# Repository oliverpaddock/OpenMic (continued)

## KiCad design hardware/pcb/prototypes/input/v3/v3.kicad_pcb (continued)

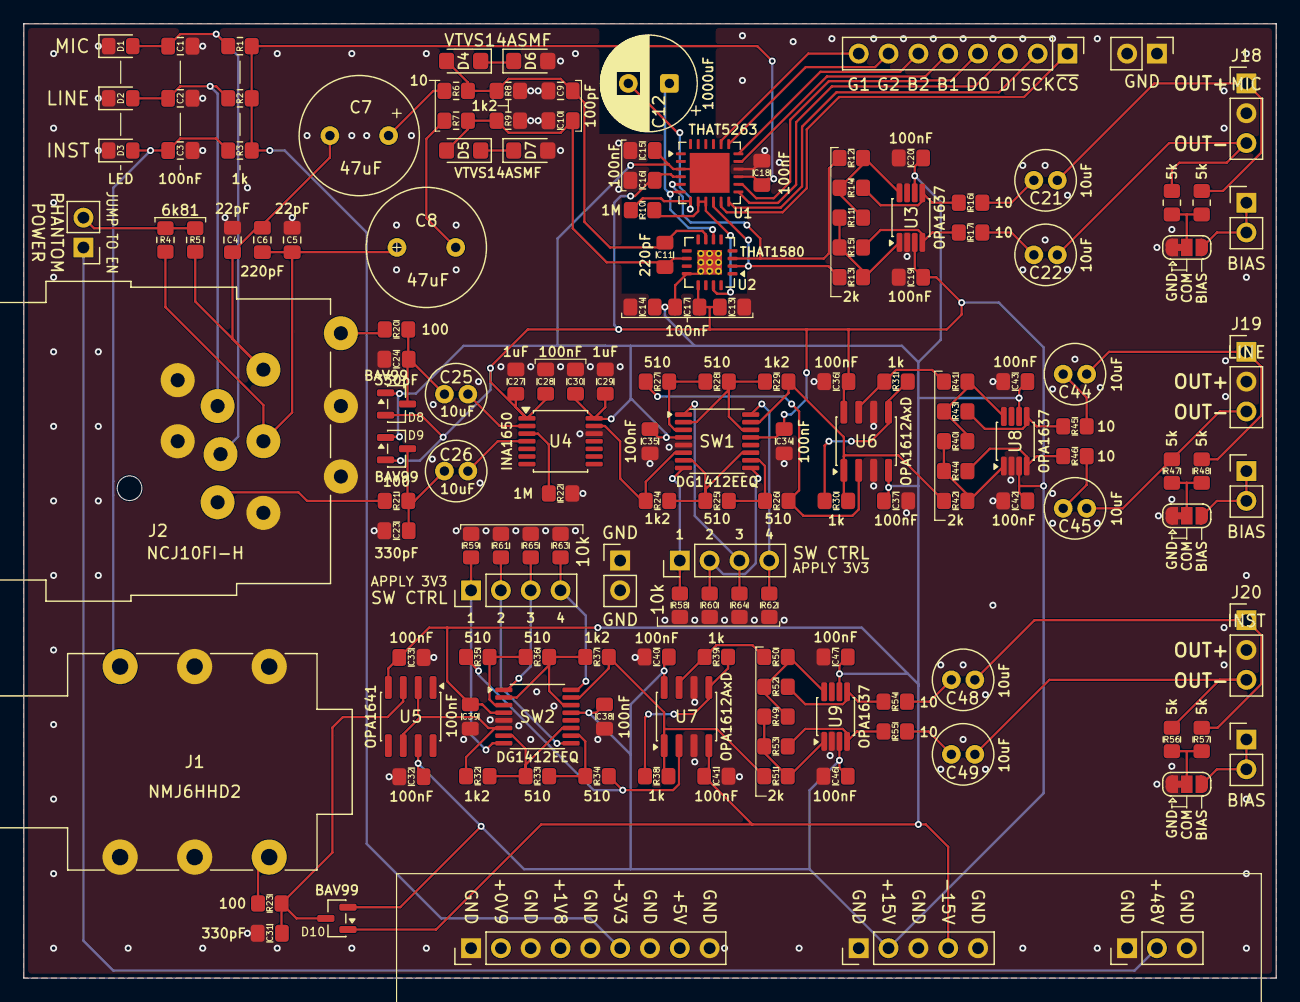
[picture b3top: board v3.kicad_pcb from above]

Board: 4 copper layers, 106.7 x 81.3 mm, 155 parts (0 on the bottom side), 95 nets.

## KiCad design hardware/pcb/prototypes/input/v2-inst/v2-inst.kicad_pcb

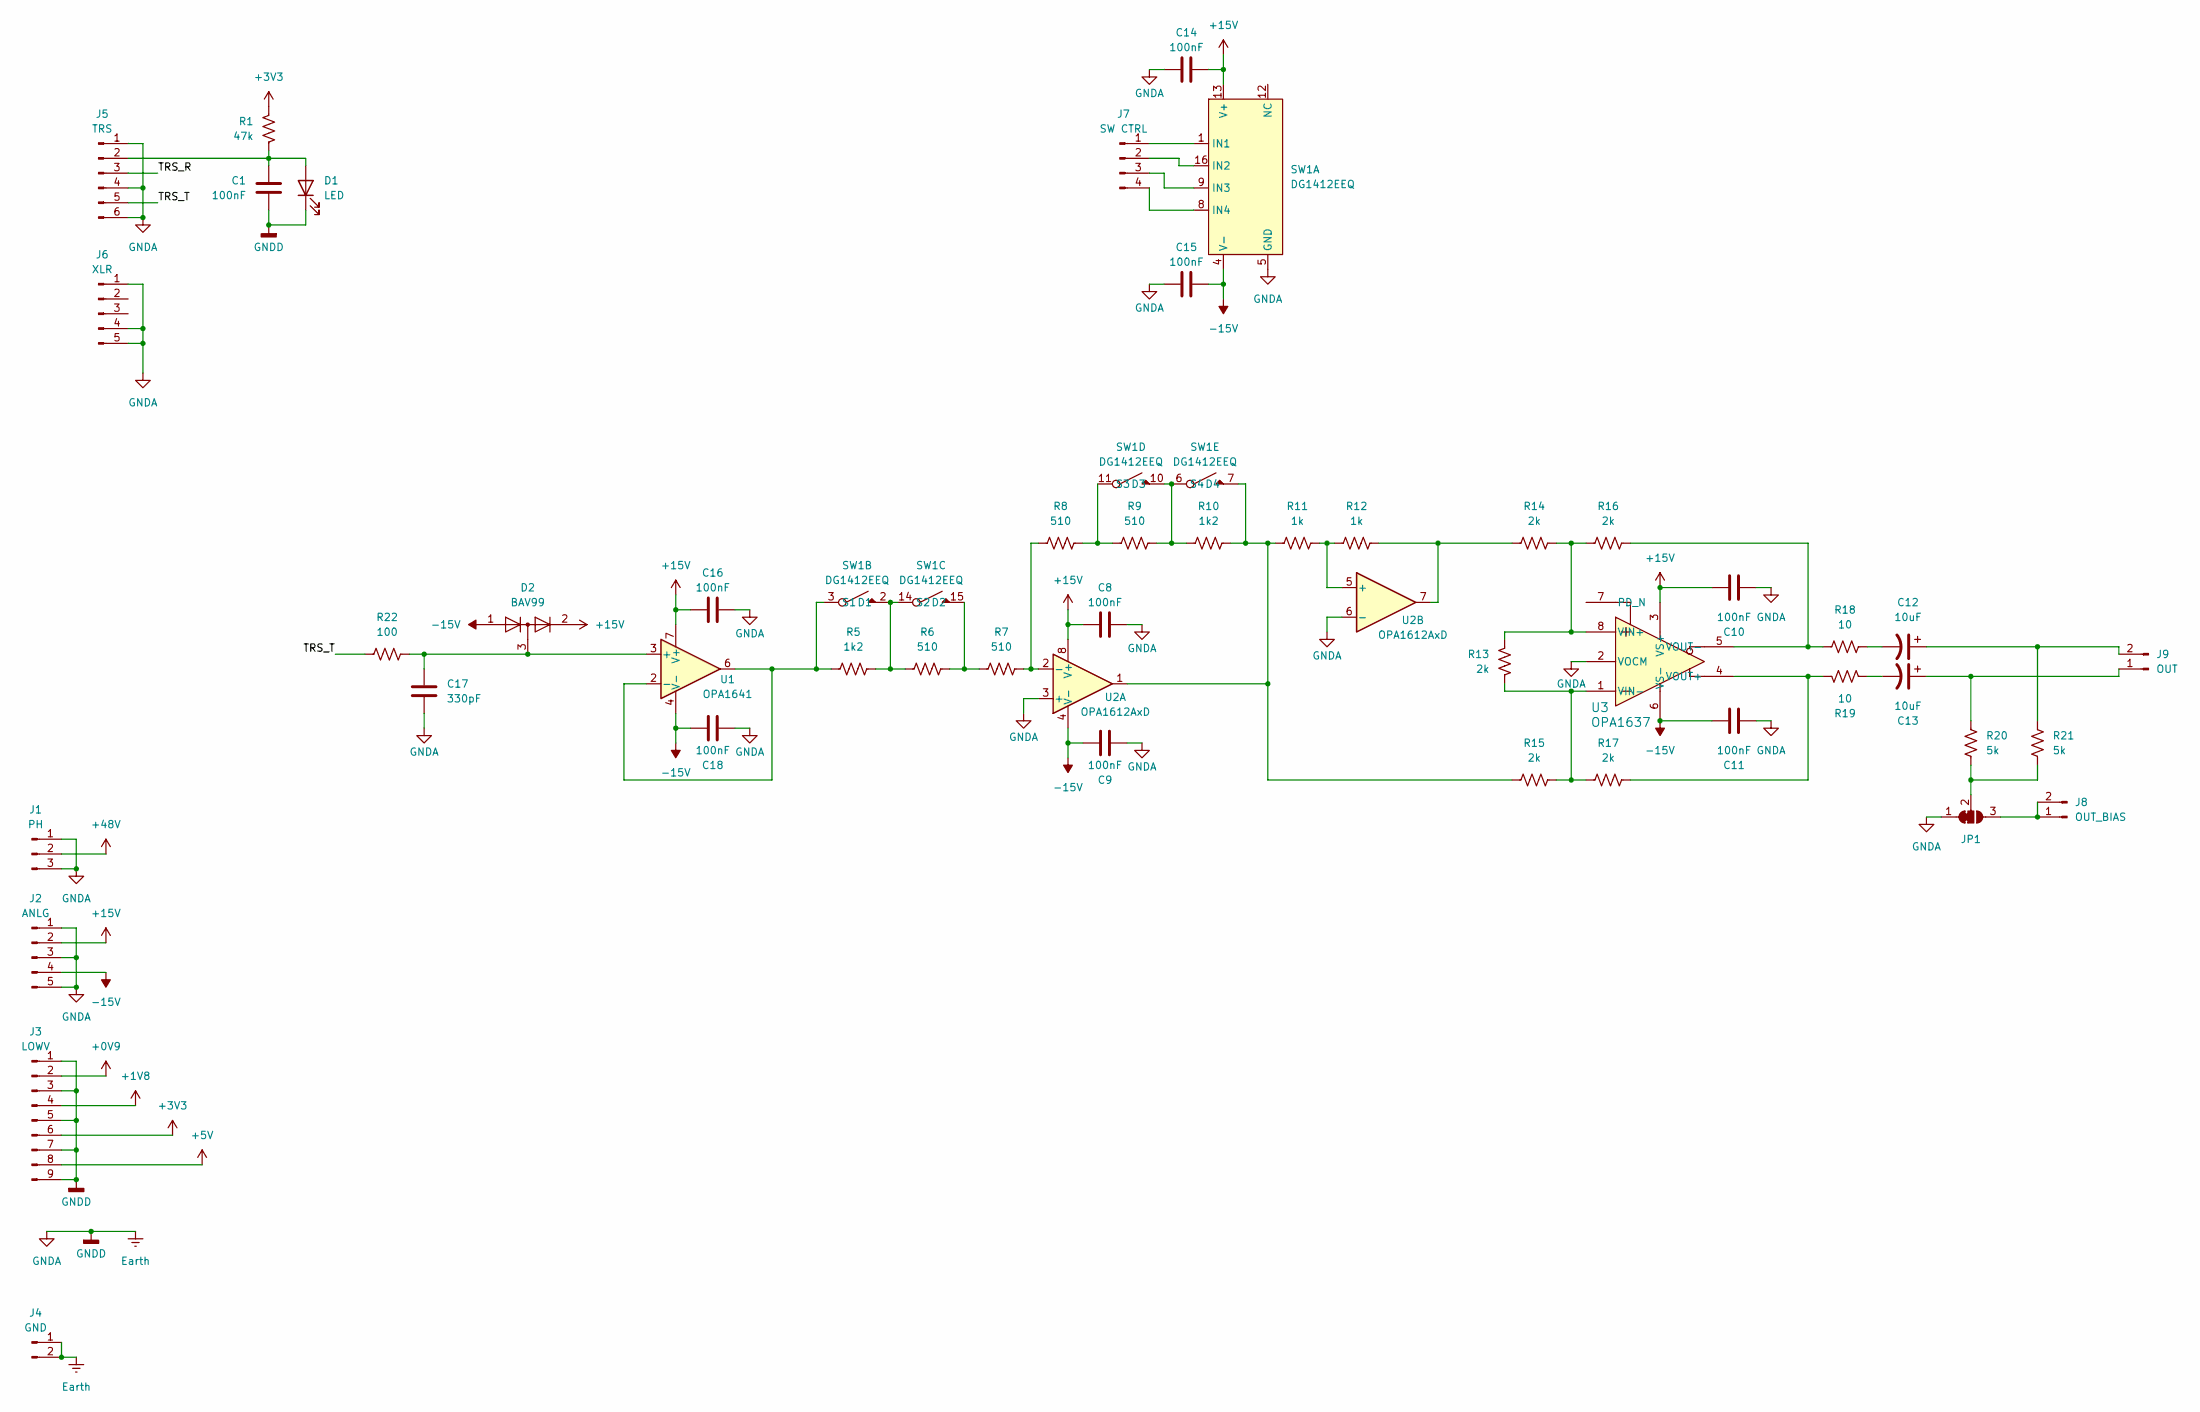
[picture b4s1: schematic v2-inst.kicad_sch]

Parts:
C1, C10, C11: 100nF; C_0805_2012Metric_Pad1.18x1.45mm_HandSolder; Voltage 6
C8, C9, C14, C15, C16, C18: 100nF; C_0805_2012Metric_Pad1.18x1.45mm_HandSolder; Voltage 50
C12, C13: 10uF; C_Radial_D5.0mm_H11.0mm_P2.00mm; Voltage 50
C17: 330pF; C_0805_2012Metric_Pad1.18x1.45mm_HandSolder; Voltage 6
D1: LED; LED_0805_2012Metric_Pad1.15x1.40mm_HandSolder
D2: BAV99; SOT-23
J1: PH; PinHeader_1x03_P2.54mm_Vertical
J2: ANLG; PinHeader_1x05_P2.54mm_Vertical
J3: LOWV; PinHeader_1x09_P2.54mm_Vertical
J4: GND; PinHeader_1x02_P2.54mm_Vertical
J5: TRS; PinHeader_1x06_P2.54mm_Vertical
J6: XLR; PinHeader_1x05_P2.54mm_Vertical
J7: SW CTRL; PinHeader_1x04_P2.54mm_Vertical
J8: OUT_BIAS; PinHeader_1x02_P2.54mm_Vertical
J9: OUT; PinHeader_1x02_P2.54mm_Vertical
JP1: SolderJumper_3_Bridged12; SolderJumper-3_P1.3mm_Bridged12_RoundedPad1.0x1.5mm
R1: 47k; R_0805_2012Metric_Pad1.20x1.40mm_HandSolder
R5, R10: 1k2; R_0805_2012Metric_Pad1.20x1.40mm_HandSolder
R6, R7, R8, R9: 510; R_0805_2012Metric_Pad1.20x1.40mm_HandSolder
R11, R12: 1k; R_0805_2012Metric_Pad1.20x1.40mm_HandSolder
R13, R14, R15, R16, R17: 2k; R_0805_2012Metric_Pad1.20x1.40mm_HandSolder
R18, R19: 10; R_0805_2012Metric_Pad1.20x1.40mm_HandSolder
R20, R21: 5k; R_0805_2012Metric_Pad1.20x1.40mm_HandSolder
R22: 100; R_0805_2012Metric_Pad1.20x1.40mm_HandSolder
SW1: DG1412EEQ; TSSOP-16_4.4x5mm_P0.65mm
U1: OPA1641; SOIC-8_3.9x4.9mm_P1.27mm
U2: OPA1612AxD; SOIC-8_3.9x4.9mm_P1.27mm
U3: OPA1637; VSSOP-8_3x3mm_P0.65mm

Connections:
+0V9: J3.2
+1V8: J3.4
+3V3: J3.6, R1.1
+5V: J3.8
+15V: C8.2, C10.1, C14.2, C16.2, D2.2 (A), J2.2, SW1.13 (V+), U1.7 (V+), U2.8 (V+), U3.3 (VS+)
+48V: J1.2
-15V: C9.2, C11.1, C15.2, C18.2, D2.1 (K), J2.4, SW1.4 (V-), U1.4 (V-), U2.4 (V-), U3.6 (VS-)
/TRS_R: J5.3
/TRS_T: J5.5, R22.2
Earth: C1.2, C8.1, C9.1, C10.2, C11.2, C14.1, C15.1, C16.1, C17.2, C18.1, D1.1 (K), J1.1, J1.3, J2.1, J2.3, J2.5, J3.1, J3.3, J3.5, J3.7, J3.9, J4.1, J4.2, J5.1, J5.4, J5.6, J6.1, J6.4, J6.5, JP1.1 (A), SW1.5 (GND), U2.3 (+), U2.6 (-), U3.2 (VOCM)
unnamed: C12.2, R18.2
unnamed: C13.2, R19.2
unnamed: C1.1, D1.2 (A), J5.2, R1.2
unnamed: J7.1, SW1.1 (IN1)
unnamed: J7.2, SW1.16 (IN2)
unnamed: J7.3, SW1.9 (IN3)
unnamed: J7.4, SW1.8 (IN4)
unnamed: J8.1, J8.2, JP1.3 (B)
unnamed: C13.1, J9.1, R20.2
unnamed: C12.1, J9.2, R21.2
unnamed: JP1.2 (C), R20.1, R21.1
unnamed: R12.1, R14.1, U2.7
unnamed: R5.1, R6.2, SW1.2 (D1), SW1.14 (S2)
unnamed: R5.2, SW1.3 (S1), U1.2 (-), U1.6
unnamed: R6.1, R7.2, SW1.15 (D2)
unnamed: R9.1, R10.2, SW1.6 (S4), SW1.10 (D3)
unnamed: R8.1, R9.2, SW1.11 (S3)
unnamed: R10.1, R11.2, R15.1, SW1.7 (D4), U2.1
unnamed: C17.1, D2.3 (K), R22.1, U1.3 (+)
unnamed: R7.1, R8.2, U2.2 (-)
unnamed: R11.1, R12.2, U2.5 (+)
unnamed: R13.2, R14.2, R16.1, U3.8 (VIN+)
unnamed: R13.1, R15.2, R17.1, U3.1 (VIN-)
unnamed: R17.2, R19.1, U3.4 (VOUT+)
unnamed: R16.2, R18.1, U3.5 (VOUT-)

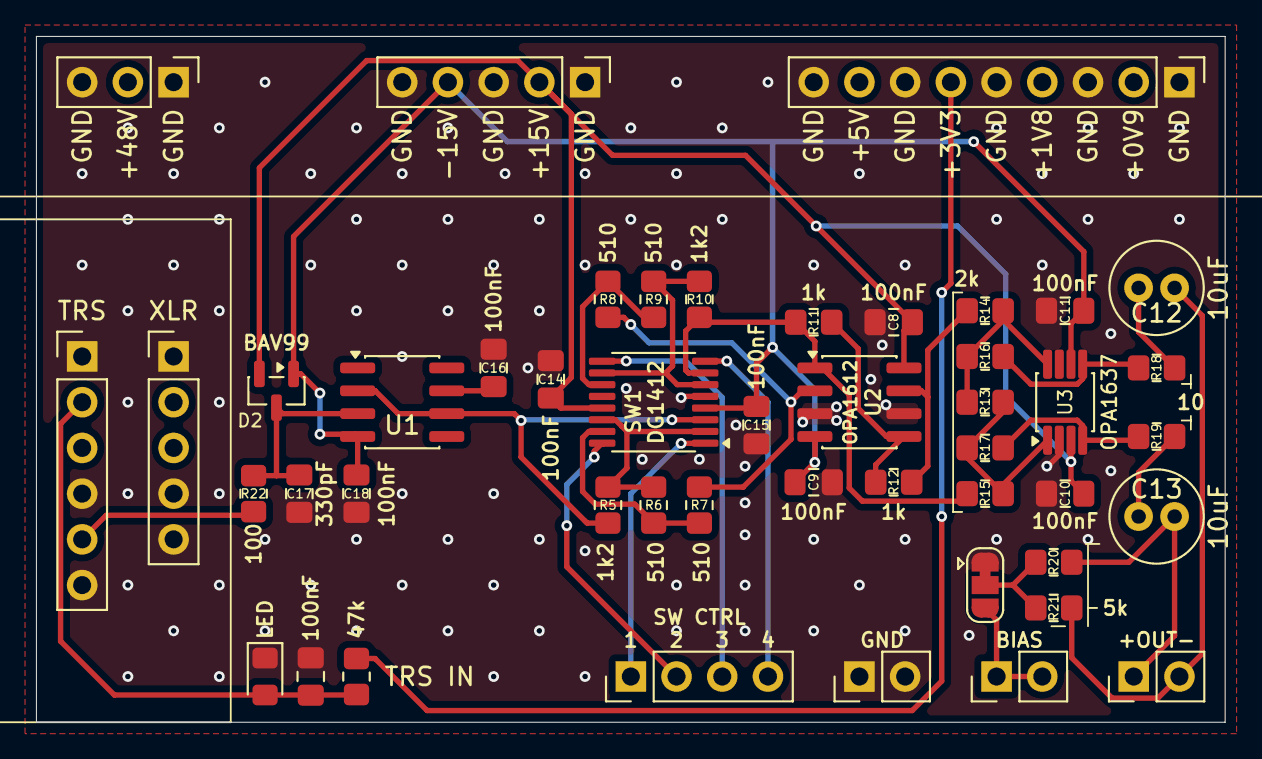
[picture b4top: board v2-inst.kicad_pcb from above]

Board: 2 copper layers, 66.0 x 38.1 mm, 47 parts (0 on the bottom side), 30 nets.

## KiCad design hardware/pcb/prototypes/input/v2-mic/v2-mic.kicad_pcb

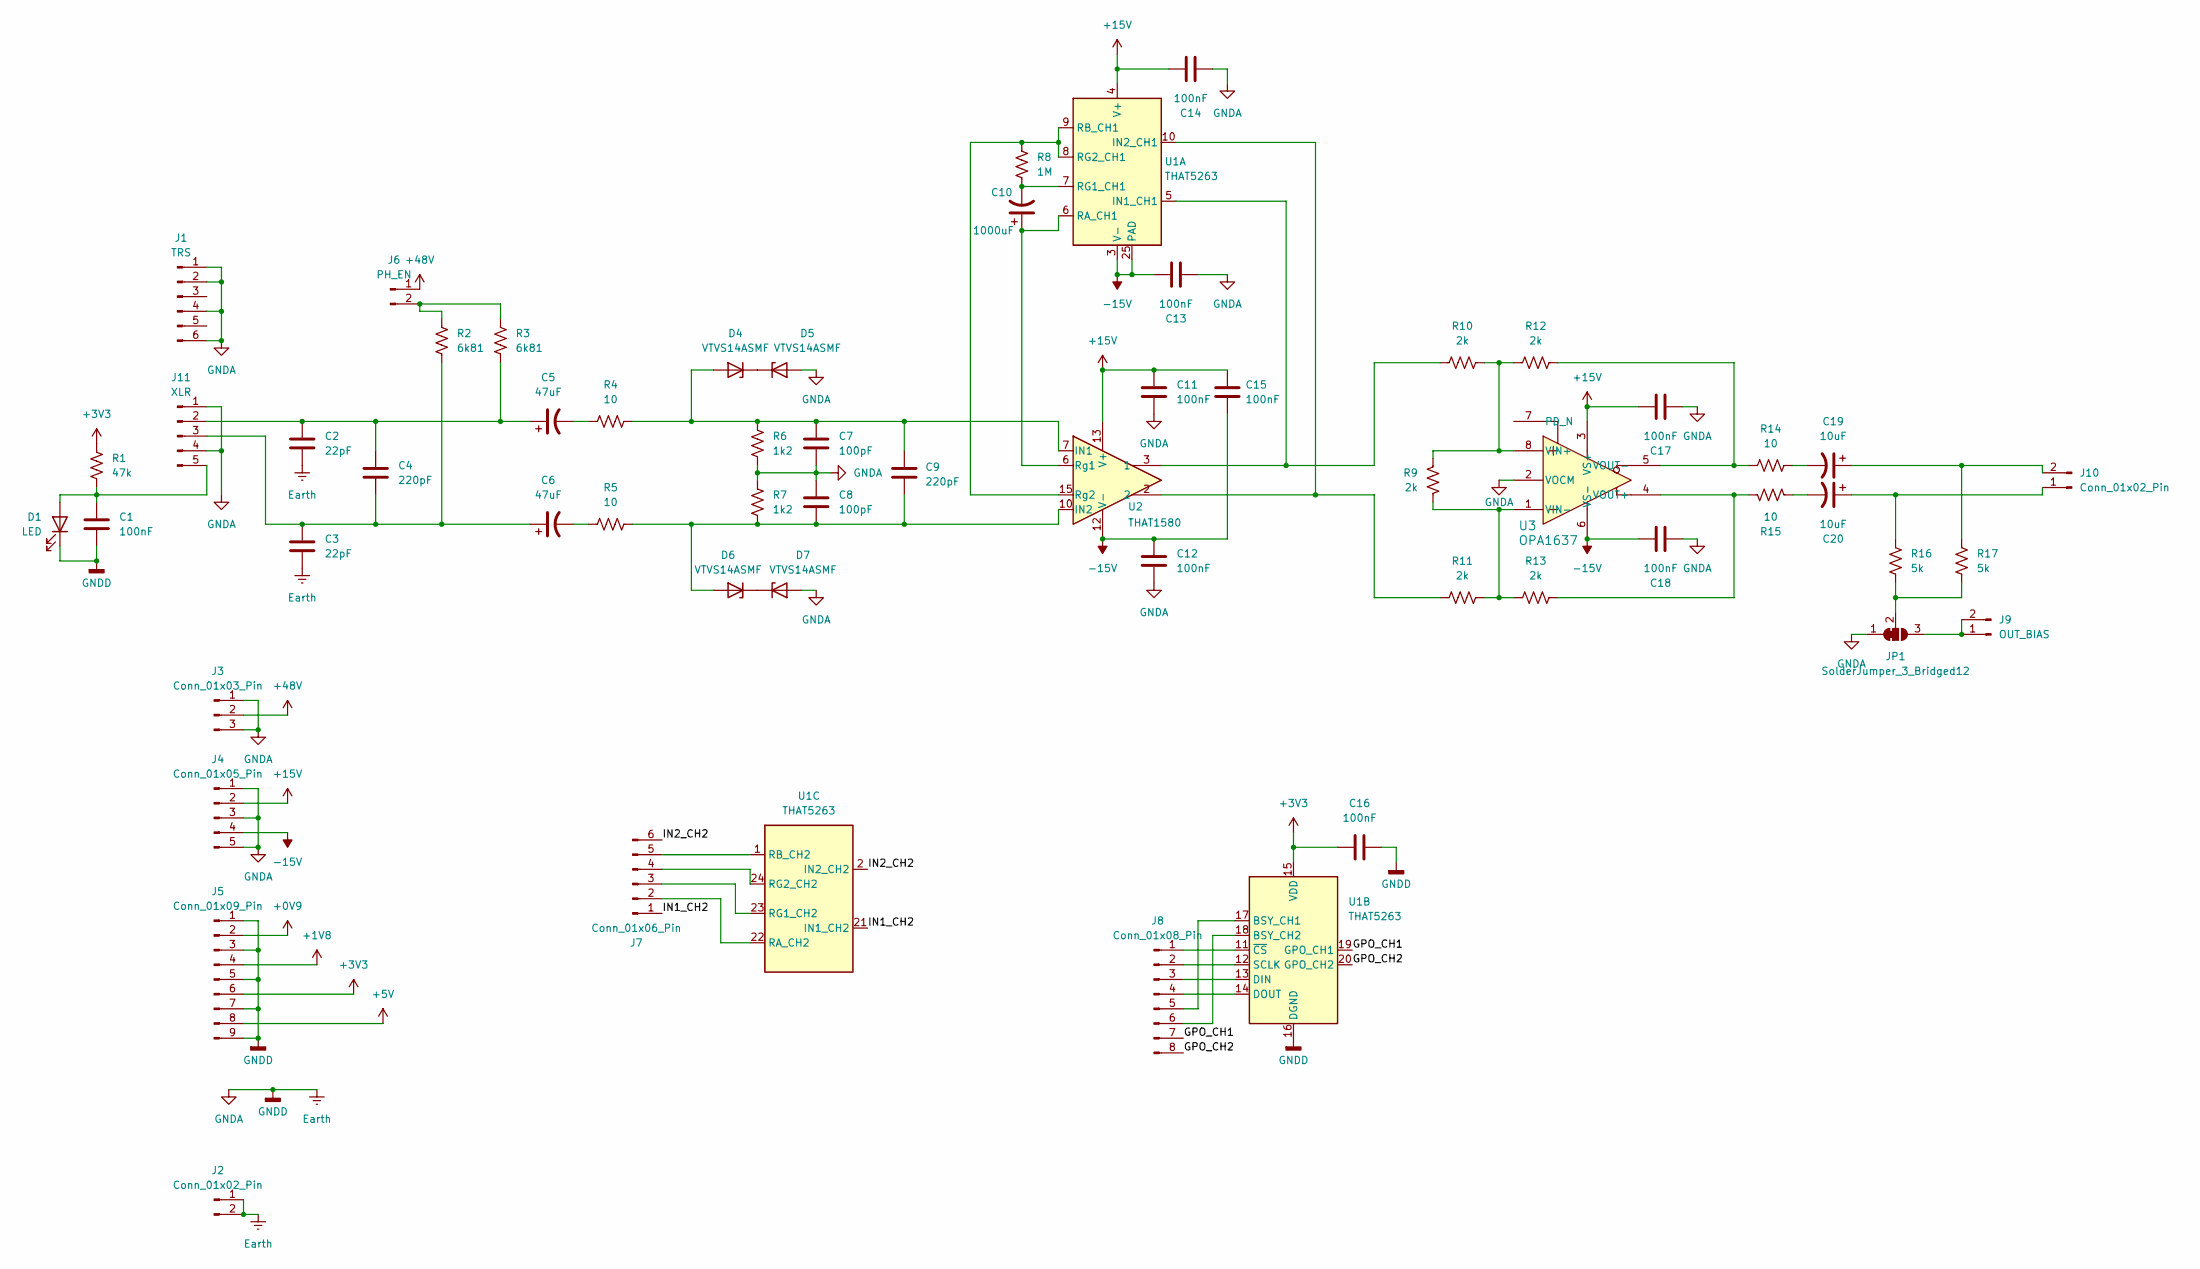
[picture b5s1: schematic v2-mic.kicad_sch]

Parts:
C1, C11, C12, C13, C14, C15, C16, C17, C18: 100nF; C_0805_2012Metric_Pad1.18x1.45mm_HandSolder; Voltage 6
C2, C3: 22pF; C_0805_2012Metric_Pad1.18x1.45mm_HandSolder; Voltage 50
C4, C9: 220pF; C_0805_2012Metric_Pad1.18x1.45mm_HandSolder; Voltage 50
C5, C6: 47uF; C_Radial_D10.0mm_H12.5mm_P5.00mm; Voltage 50
C7, C8: 100pF; C_0805_2012Metric_Pad1.18x1.45mm_HandSolder; Voltage 50
C10: 1000uF; CP_Radial_D8.0mm_P3.50mm; Voltage 6.3
C19, C20: 10uF; C_Radial_D5.0mm_H11.0mm_P2.00mm; Voltage 50
D1: LED; LED_0805_2012Metric_Pad1.15x1.40mm_HandSolder
D4, D5, D6, D7: VTVS14ASMF; D_SMF
J1: TRS; PinHeader_1x06_P2.54mm_Vertical
J2, J10: Conn_01x02_Pin; PinHeader_1x02_P2.54mm_Vertical
J3: Conn_01x03_Pin; PinHeader_1x03_P2.54mm_Vertical
J4: Conn_01x05_Pin; PinHeader_1x05_P2.54mm_Vertical
J5: Conn_01x09_Pin; PinHeader_1x09_P2.54mm_Vertical
J6: PH_EN; PinHeader_1x02_P2.54mm_Vertical
J7: Conn_01x06_Pin; PinHeader_1x06_P2.54mm_Vertical
J8: Conn_01x08_Pin; PinHeader_1x08_P2.54mm_Vertical
J9: OUT_BIAS; PinHeader_1x02_P2.54mm_Vertical
J11: XLR; PinHeader_1x05_P2.54mm_Vertical
JP1: SolderJumper_3_Bridged12; SolderJumper-3_P1.3mm_Bridged12_RoundedPad1.0x1.5mm
R1: 47k; R_0805_2012Metric_Pad1.20x1.40mm_HandSolder
R2, R3: 6k81; R_0805_2012Metric_Pad1.20x1.40mm_HandSolder
R4, R5, R14, R15: 10; R_0805_2012Metric_Pad1.20x1.40mm_HandSolder
R6, R7: 1k2; R_0805_2012Metric_Pad1.20x1.40mm_HandSolder
R8: 1M; R_0805_2012Metric_Pad1.20x1.40mm_HandSolder
R9, R10, R11, R12, R13: 2k; R_0805_2012Metric_Pad1.20x1.40mm_HandSolder
R16, R17: 5k; R_0805_2012Metric_Pad1.20x1.40mm_HandSolder
U1: THAT5263; QFN-24-1EP_5x5mm_P0.65mm_EP3.4x3.4mm
U2: THAT1580; QFN-16-1EP_4x4mm_P0.65mm_EP2.1x2.1mm_ThermalVias
U3: OPA1637; VSSOP-8_3x3mm_P0.65mm

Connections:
+0V9: J5.2
+1V8: J5.4
+3V3: C16.1, J5.6, R1.1, U1.15 (VDD)
+5V: J5.8
+15V: C11.1, C14.1, C15.1, C17.1, J4.2, U1.4 (V+), U2.13 (V+), U3.3 (VS+)
+48V: J3.2, J6.1
-15V: C12.1, C13.1, C15.2, C18.1, J4.4, U1.3 (V-), U1.25 (PAD), U2.12 (V-), U2.17 (V-), U3.6 (VS-)
/GPO_CH1: J8.7, U1.19 (GPO_CH1)
/GPO_CH2: J8.8, U1.20 (GPO_CH2)
/IN1_CH2: J7.1, U1.21 (IN1_CH2)
/IN2_CH2: J7.6, U1.2 (IN2_CH2)
Earth: C1.2, C2.2, C3.2, C7.2, C8.1, C11.2, C12.2, C13.2, C14.2, C16.2, C17.2, C18.2, D1.1 (K), D5.2 (A), D7.2 (A), J1.1, J1.2, J1.4, J1.6, J2.1, J2.2, J3.1, J3.3, J4.1, J4.3, J4.5, J5.1, J5.3, J5.5, J5.7, J5.9, J11.1, J11.4, JP1.1 (A), R6.1, R7.2, U1.16 (DGND), U3.2 (VOCM)
unnamed: C5.2, R4.1
unnamed: C6.2, R5.1
unnamed: C19.2, R14.2
unnamed: C20.2, R15.2
unnamed: C1.1, D1.2 (A), J11.5, R1.2
unnamed: C7.1, C9.1, D4.2 (A), R4.2, R6.2, U2.7 (IN1)
unnamed: D4.1 (K), D5.1 (K)
unnamed: C8.2, C9.2, D6.2 (A), R5.2, R7.1, U2.10 (IN2)
unnamed: D6.1 (K), D7.1 (K)
unnamed: J6.2, R2.1, R3.1
unnamed: J7.2, U1.22 (RA_CH2)
unnamed: J7.3, U1.23 (RG1_CH2)
unnamed: J7.4, U1.24 (RG2_CH2)
unnamed: J7.5, U1.1 (RB_CH2)
unnamed: J8.1, U1.11 (~CS)
unnamed: J8.2, U1.12 (SCLK)
unnamed: J8.3, U1.13 (DIN)
unnamed: J8.4, U1.14 (DOUT)
unnamed: J8.5, U1.17 (BSY_CH1)
unnamed: J8.6, U1.18 (BSY_CH2)
unnamed: J9.1, J9.2, JP1.3 (B)
unnamed: C20.1, J10.1, R16.2
unnamed: C19.1, J10.2, R17.2
unnamed: C2.1, C4.1, C5.1, J11.2, R3.2
unnamed: C3.1, C4.2, C6.1, J11.3, R2.2
unnamed: JP1.2 (C), R16.1, R17.1
unnamed: R10.1, U1.5 (IN1_CH1), U2.3 (1)
unnamed: R11.1, U1.10 (IN2_CH1), U2.2
unnamed: C10.1, U1.6 (RA_CH1), U2.6 (Rg1)
unnamed: R8.2, U1.8 (RG2_CH1), U1.9 (RB_CH1), U2.15 (Rg2)
unnamed: C10.2, R8.1, U1.7 (RG1_CH1)
unnamed: R9.2, R10.2, R12.1, U3.8 (VIN+)
unnamed: R9.1, R11.2, R13.1, U3.1 (VIN-)
unnamed: R13.2, R15.1, U3.4 (VOUT+)
unnamed: R12.2, R14.1, U3.5 (VOUT-)

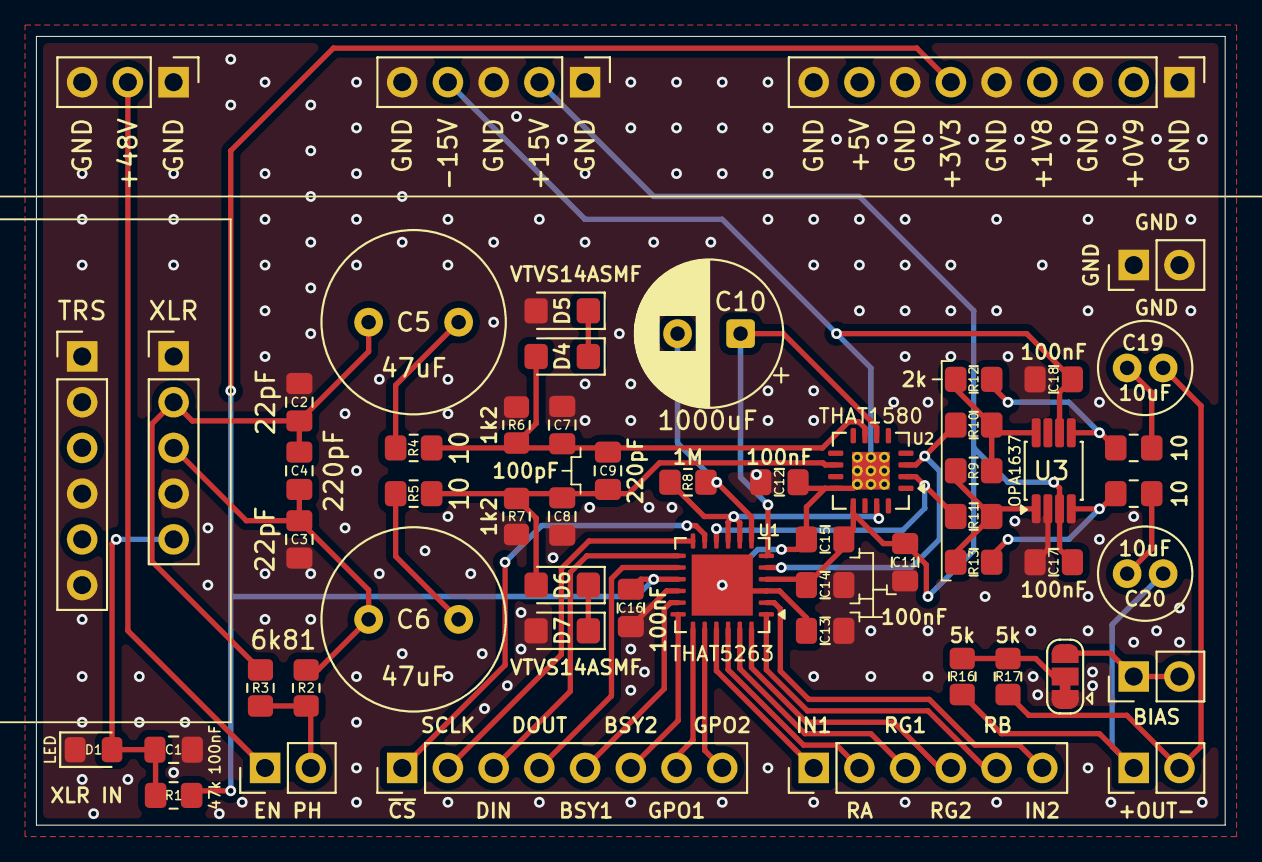
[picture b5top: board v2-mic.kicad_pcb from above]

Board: 2 copper layers, 66.0 x 43.8 mm, 57 parts (0 on the bottom side), 44 nets.

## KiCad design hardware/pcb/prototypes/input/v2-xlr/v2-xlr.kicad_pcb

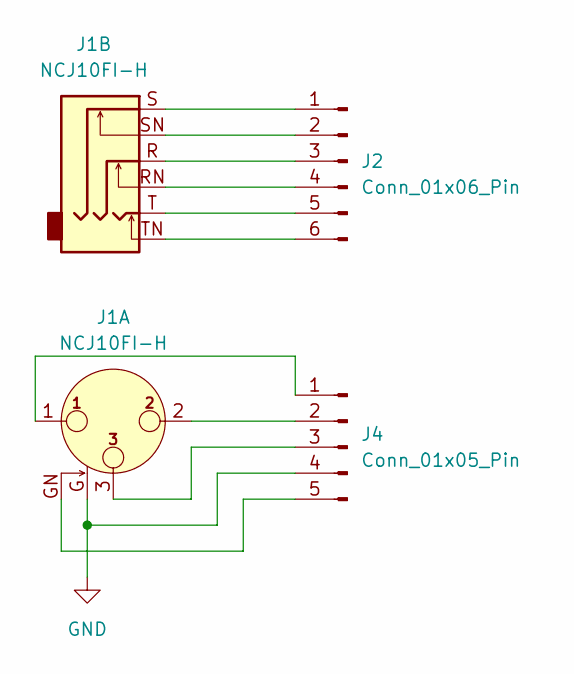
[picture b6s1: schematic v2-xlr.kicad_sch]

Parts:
J1: NCJ10FI-H; Jack_XLR-6.35mm_Neutrik_NCJ10FI-H_Horizontal
J2: Conn_01x06_Pin; PinHeader_1x06_P2.54mm_Vertical
J4: Conn_01x05_Pin; PinHeader_1x05_P2.54mm_Vertical

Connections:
GND: J1.G, J4.4
unnamed: J1.S, J2.1
unnamed: J1.SN, J2.2
unnamed: J1.R, J2.3
unnamed: J1.RN, J2.4
unnamed: J1.T, J2.5
unnamed: J1.TN, J2.6
unnamed: J1.1, J4.1
unnamed: J1.2, J4.2
unnamed: J1.3, J4.3
unnamed: J1.GN, J4.5

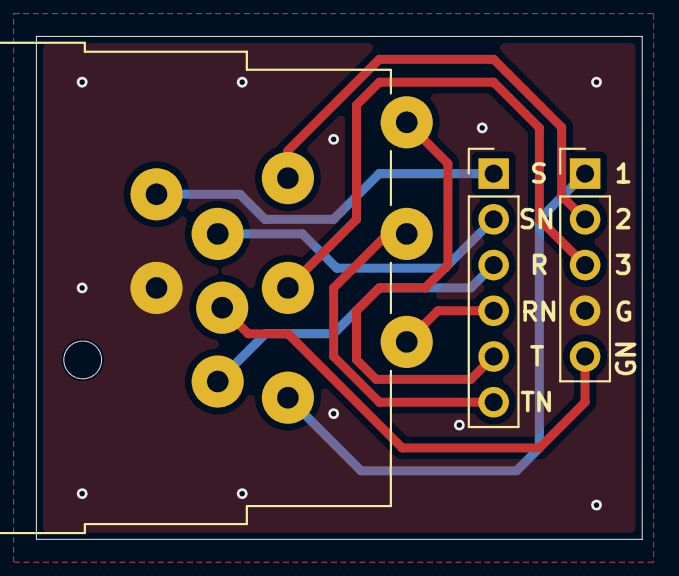
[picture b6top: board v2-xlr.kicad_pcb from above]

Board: 2 copper layers, 33.7 x 27.9 mm, 3 parts (0 on the bottom side), 11 nets.

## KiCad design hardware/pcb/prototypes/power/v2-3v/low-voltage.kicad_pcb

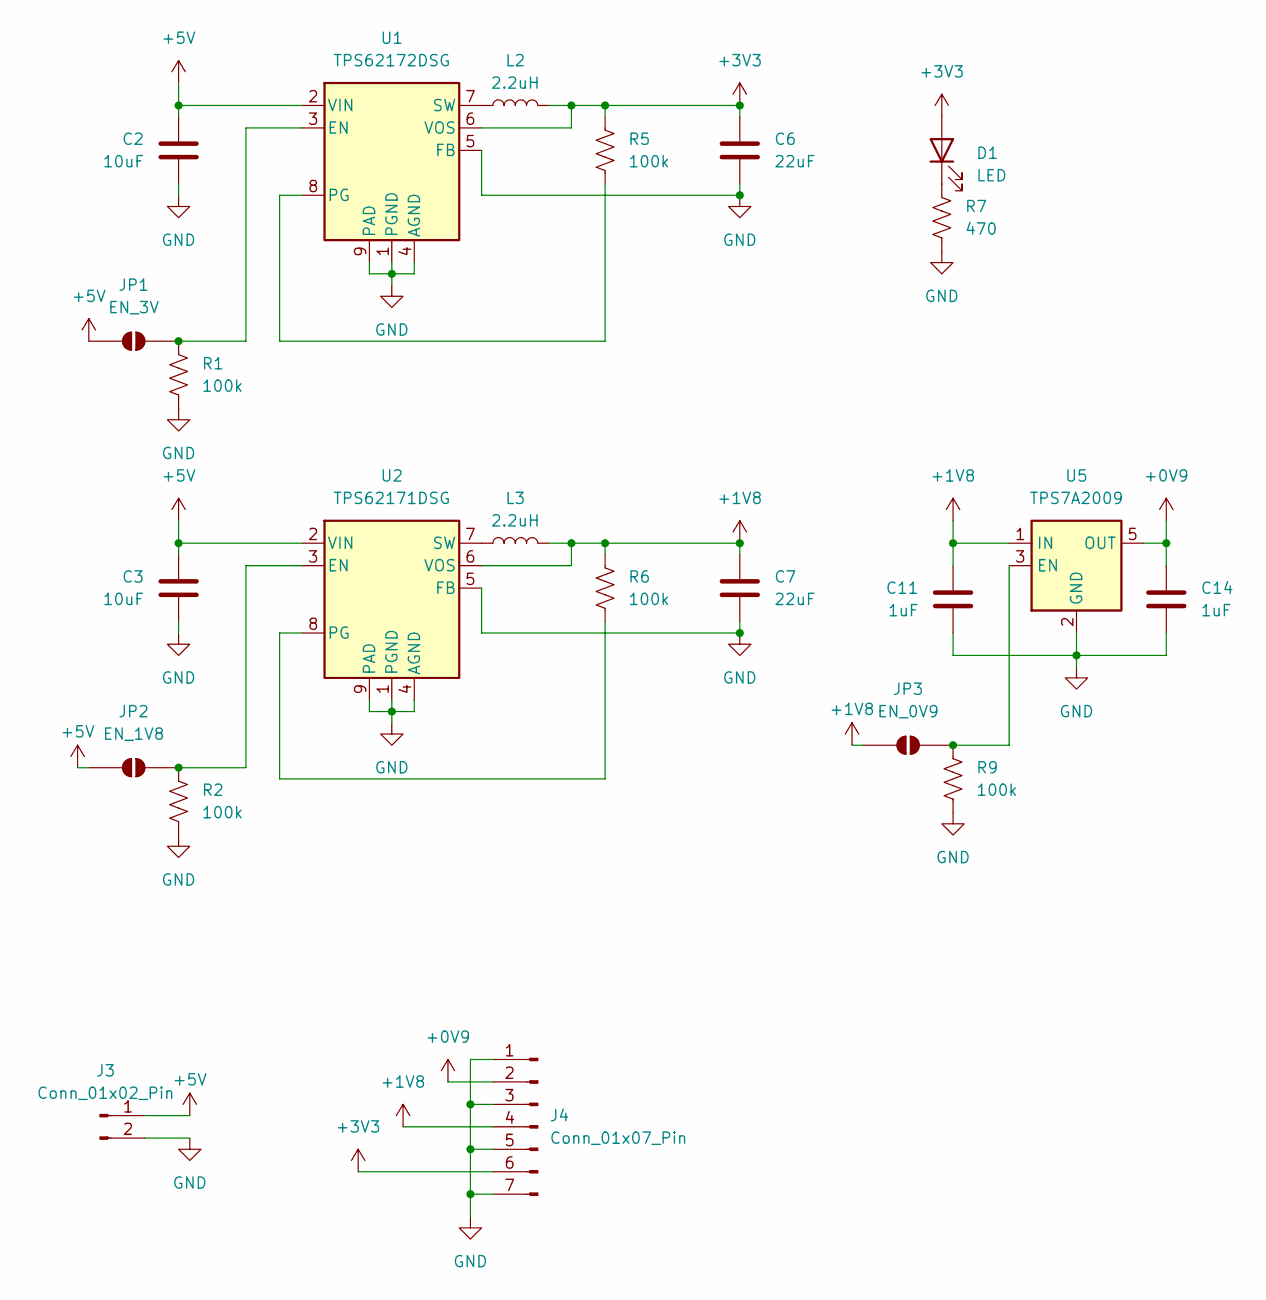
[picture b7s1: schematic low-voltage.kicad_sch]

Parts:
C2, C3: 10uF; C_0805_2012Metric_Pad1.18x1.45mm_HandSolder; MPN CL21A106KAYNNNE; LCSC C15850
C6, C7: 22uF; C_0805_2012Metric_Pad1.18x1.45mm_HandSolder; MPN CL21A226MAQNNNE; LCSC C45783
C11, C14: 1uF; C_0805_2012Metric_Pad1.18x1.45mm_HandSolder; MPN CL21B105KBFNNNE; LCSC C28323
D1: LED; LED_0805_2012Metric_Pad1.15x1.40mm_HandSolder
J3: Conn_01x02_Pin; PinHeader_1x02_P2.54mm_Vertical
J4: Conn_01x07_Pin; PinHeader_1x07_P2.54mm_Vertical
JP1: EN_3V; SolderJumper-2_P1.3mm_Open_RoundedPad1.0x1.5mm
JP2: EN_1V8; SolderJumper-2_P1.3mm_Open_RoundedPad1.0x1.5mm
JP3: EN_0V9; SolderJumper-2_P1.3mm_Open_RoundedPad1.0x1.5mm
L2, L3: 2.2uH; L_Wurth_WE-LQSH-3012; MPN ANR3015T2R2M; LCSC C6364793
R1, R2, R5, R6, R9: 100k; R_0805_2012Metric_Pad1.20x1.40mm_HandSolder; MPN 0805W8F1003T5E; LCSC C149504
R7: 470; R_0805_2012Metric_Pad1.20x1.40mm_HandSolder; MPN 0805W8F1003T5E; LCSC C149504
U1: TPS62172DSG; WSON-8-1EP_2x2mm_P0.5mm_EP0.9x1.6mm_ThermalVias; MPN TPS62172DSGR; LCSC C59873
U2: TPS62171DSG; WSON-8-1EP_2x2mm_P0.5mm_EP0.9x1.6mm_ThermalVias; MPN TPS62171DSGR; LCSC C2071102
U5: TPS7A2009; SOT-23-5; MPN TPS7A2009PDBVR; LCSC C2861215

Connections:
+0V9: C14.1, J4.2, U5.5 (OUT)
+1V8: C7.1, C11.1, J4.4, JP3.1 (A), L3.2, R6.1, U2.6 (VOS), U5.1 (IN)
+3V3: C6.1, D1.2 (A), J4.6, L2.2, R5.1, U1.6 (VOS)
+5V: C2.1, C3.1, J3.1, JP1.1 (A), JP2.1 (A), U1.2 (VIN), U2.2 (VIN)
GND: C2.2, C3.2, C6.2, C7.2, C11.2, C14.2, J3.2, J4.1, J4.3, J4.5, J4.7, R1.2, R2.2, R7.2, R9.2, U1.1 (PGND), U1.4 (AGND), U1.5 (FB), U1.9 (PAD), U2.1 (PGND), U2.4 (AGND), U2.5 (FB), U2.9 (PAD), U5.2 (GND)
unnamed: D1.1 (K), R7.1
unnamed: JP1.2 (B), R1.1, U1.3 (EN)
unnamed: JP2.2 (B), R2.1, U2.3 (EN)
unnamed: JP3.2 (B), R9.1, U5.3 (EN)
unnamed: R5.2, U1.8 (PG)
unnamed: L2.1, U1.7 (SW)
unnamed: R6.2, U2.8 (PG)
unnamed: L3.1, U2.7 (SW)

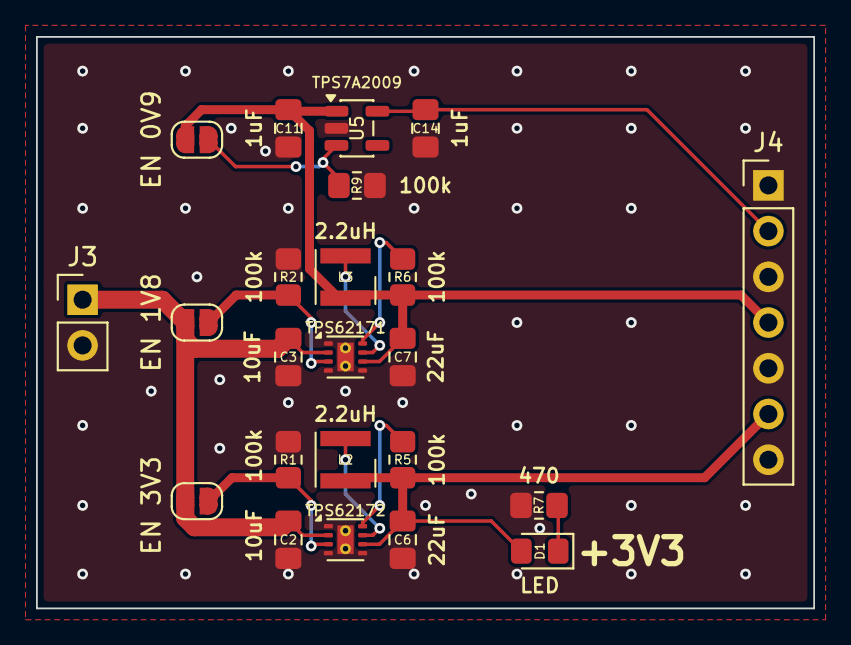
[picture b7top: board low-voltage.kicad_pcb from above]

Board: 2 copper layers, 43.2 x 31.8 mm, 23 parts (0 on the bottom side), 13 nets.

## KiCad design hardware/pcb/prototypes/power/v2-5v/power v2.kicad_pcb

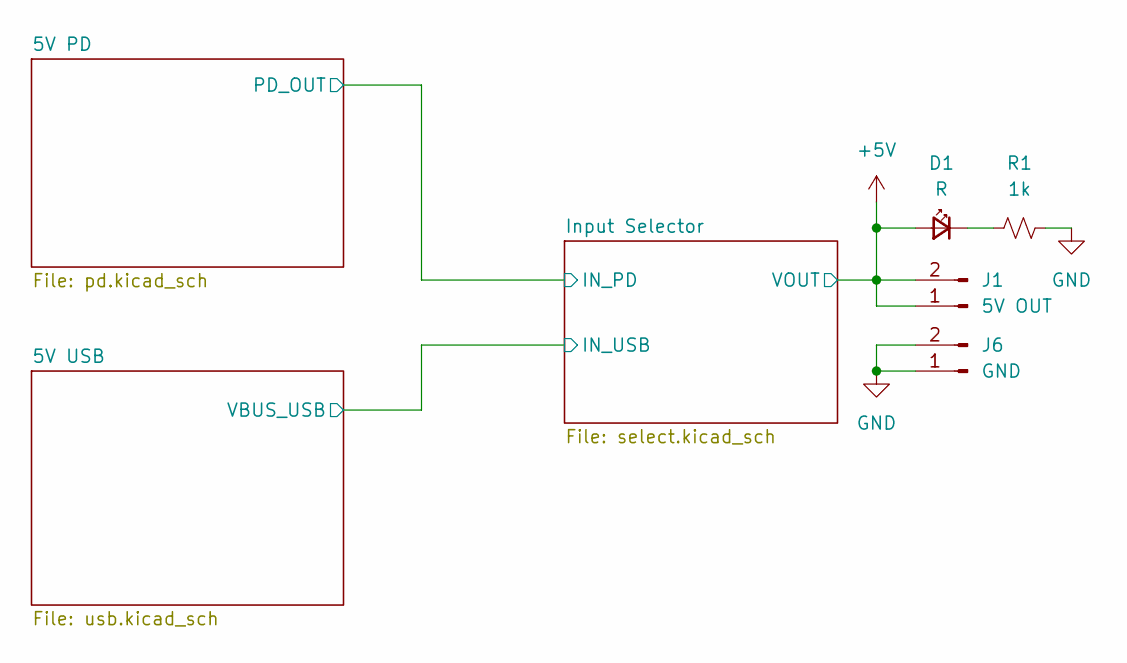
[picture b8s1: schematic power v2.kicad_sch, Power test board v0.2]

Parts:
D1: R; LED_0805_2012Metric_Pad1.15x1.40mm_HandSolder
J1: 5V OUT; PinHeader_1x02_P2.54mm_Vertical
J6: GND; PinHeader_1x02_P2.54mm_Vertical
R1: 1k; R_0805_2012Metric_Pad1.20x1.40mm_HandSolder

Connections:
+5V: D1.2 (A), J1.1, J1.2; also elsewhere on the board
GND: J6.1, J6.2, R1.2; also elsewhere on the board
unnamed: D1.1 (K), R1.1

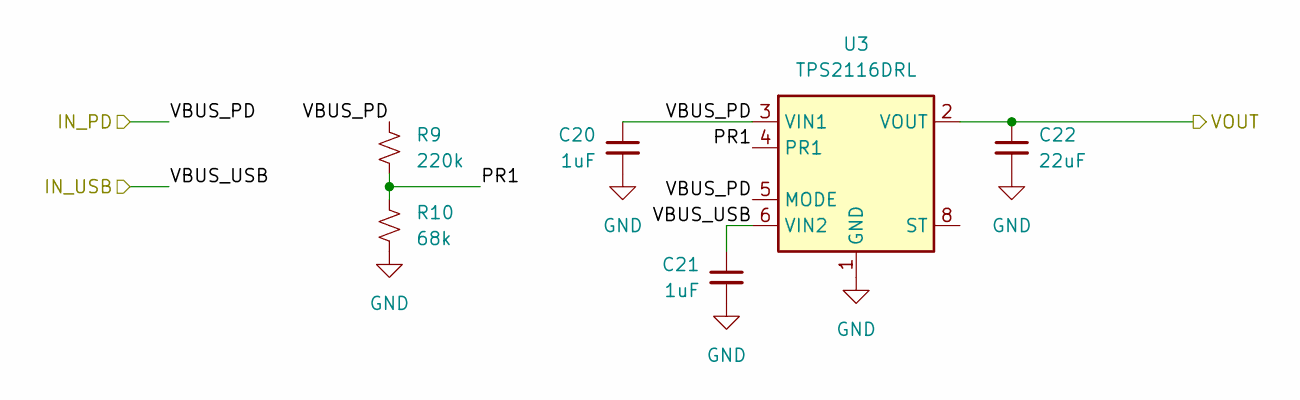
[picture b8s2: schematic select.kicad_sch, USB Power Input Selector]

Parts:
C20, C21: 1uF; C_0805_2012Metric_Pad1.18x1.45mm_HandSolder
C22: 22uF; C_0805_2012Metric_Pad1.18x1.45mm_HandSolder
R9: 220k; R_0805_2012Metric_Pad1.20x1.40mm_HandSolder
R10: 68k; R_0805_2012Metric_Pad1.20x1.40mm_HandSolder
U3: TPS2116DRL; SOT-583-8; MPN TPS2116DRLR

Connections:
+5V: C22.1, U3.2 (VOUT), U3.7 (VOUT); also elsewhere on the board
/5V PD/VSYS: C20.1, R9.1, U3.3 (VIN1), U3.5 (MODE); also elsewhere on the board
/5V USB/VBUS_USB: C21.1, U3.6 (VIN2); also elsewhere on the board
/Input Selector/PR1: R9.2, R10.1, U3.4 (PR1)
GND: C20.2, C21.2, C22.2, R10.2, U3.1 (GND); also elsewhere on the board

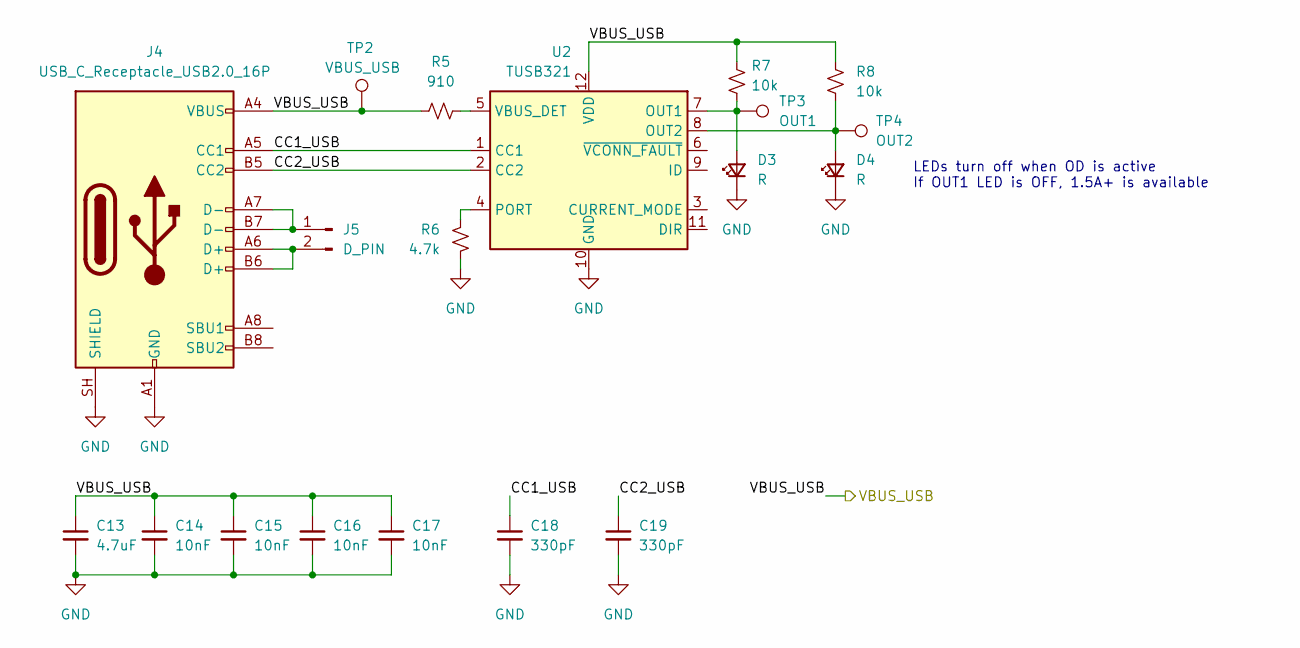
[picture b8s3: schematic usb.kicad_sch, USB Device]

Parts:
C13: 4.7uF; C_0805_2012Metric_Pad1.18x1.45mm_HandSolder; Rating 25V
C14, C15, C16, C17: 10nF; C_0805_2012Metric_Pad1.18x1.45mm_HandSolder; Rating 25V
C18, C19: 330pF; C_0805_2012Metric_Pad1.18x1.45mm_HandSolder; Rating 6.3V
D3, D4: R; LED_0805_2012Metric_Pad1.15x1.40mm_HandSolder
J4: USB_C_Receptacle_USB2.0_16P; USB_C_Receptacle_HRO_TYPE-C-31-M-12
J5: D_PIN; PinHeader_1x02_P1.00mm_Vertical
R5: 910; R_0805_2012Metric_Pad1.20x1.40mm_HandSolder
R6: 4.7k; R_0805_2012Metric_Pad1.20x1.40mm_HandSolder
R7, R8: 10k; R_0805_2012Metric_Pad1.20x1.40mm_HandSolder
TP2: VBUS_USB; TestPoint_Pad_1.5x1.5mm
TP3: OUT1; TestPoint_Pad_1.5x1.5mm
TP4: OUT2; TestPoint_Pad_1.5x1.5mm
U2: TUSB321; Texas_X2QFN-12_1.6x1.6mm_P0.4mm; MPN TUSB321RWBR

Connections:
/5V USB/CC1_USB: C18.1, J4.A5 (CC1), U2.1 (CC1)
/5V USB/CC2_USB: C19.1, J4.B5 (CC2), U2.2 (CC2)
/5V USB/VBUS_USB: C13.1, C14.1, C15.1, C16.1, C17.1, J4.A4 (VBUS), J4.A9 (VBUS), J4.B4 (VBUS), J4.B9 (VBUS), R5.1, R7.2, R8.2, TP2.1 (1_1), U2.12 (VDD); also elsewhere on the board
GND: C13.2, C14.2, C15.2, C16.2, C17.2, C18.2, C19.2, D3.1 (K), D4.1 (K), J4.A1 (GND), J4.A12 (GND), J4.B1 (GND), J4.B12 (GND), J4.SH (SHIELD), R6.1, U2.10 (GND); also elsewhere on the board
unnamed: D3.2 (A), R7.1, TP3.1 (1_1), U2.7 (OUT1)
unnamed: D4.2 (A), R8.1, TP4.1 (1_1), U2.8 (OUT2)
unnamed: J4.A7 (D-), J4.B7 (D-), J5.1
unnamed: J4.A6 (D+), J4.B6 (D+), J5.2
unnamed: R6.2, U2.4 (PORT)
unnamed: R5.2, U2.5 (VBUS_DET)

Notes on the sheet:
LEDs turn off when OD is active If OUT1 LED is OFF, 1.5A+ is available
